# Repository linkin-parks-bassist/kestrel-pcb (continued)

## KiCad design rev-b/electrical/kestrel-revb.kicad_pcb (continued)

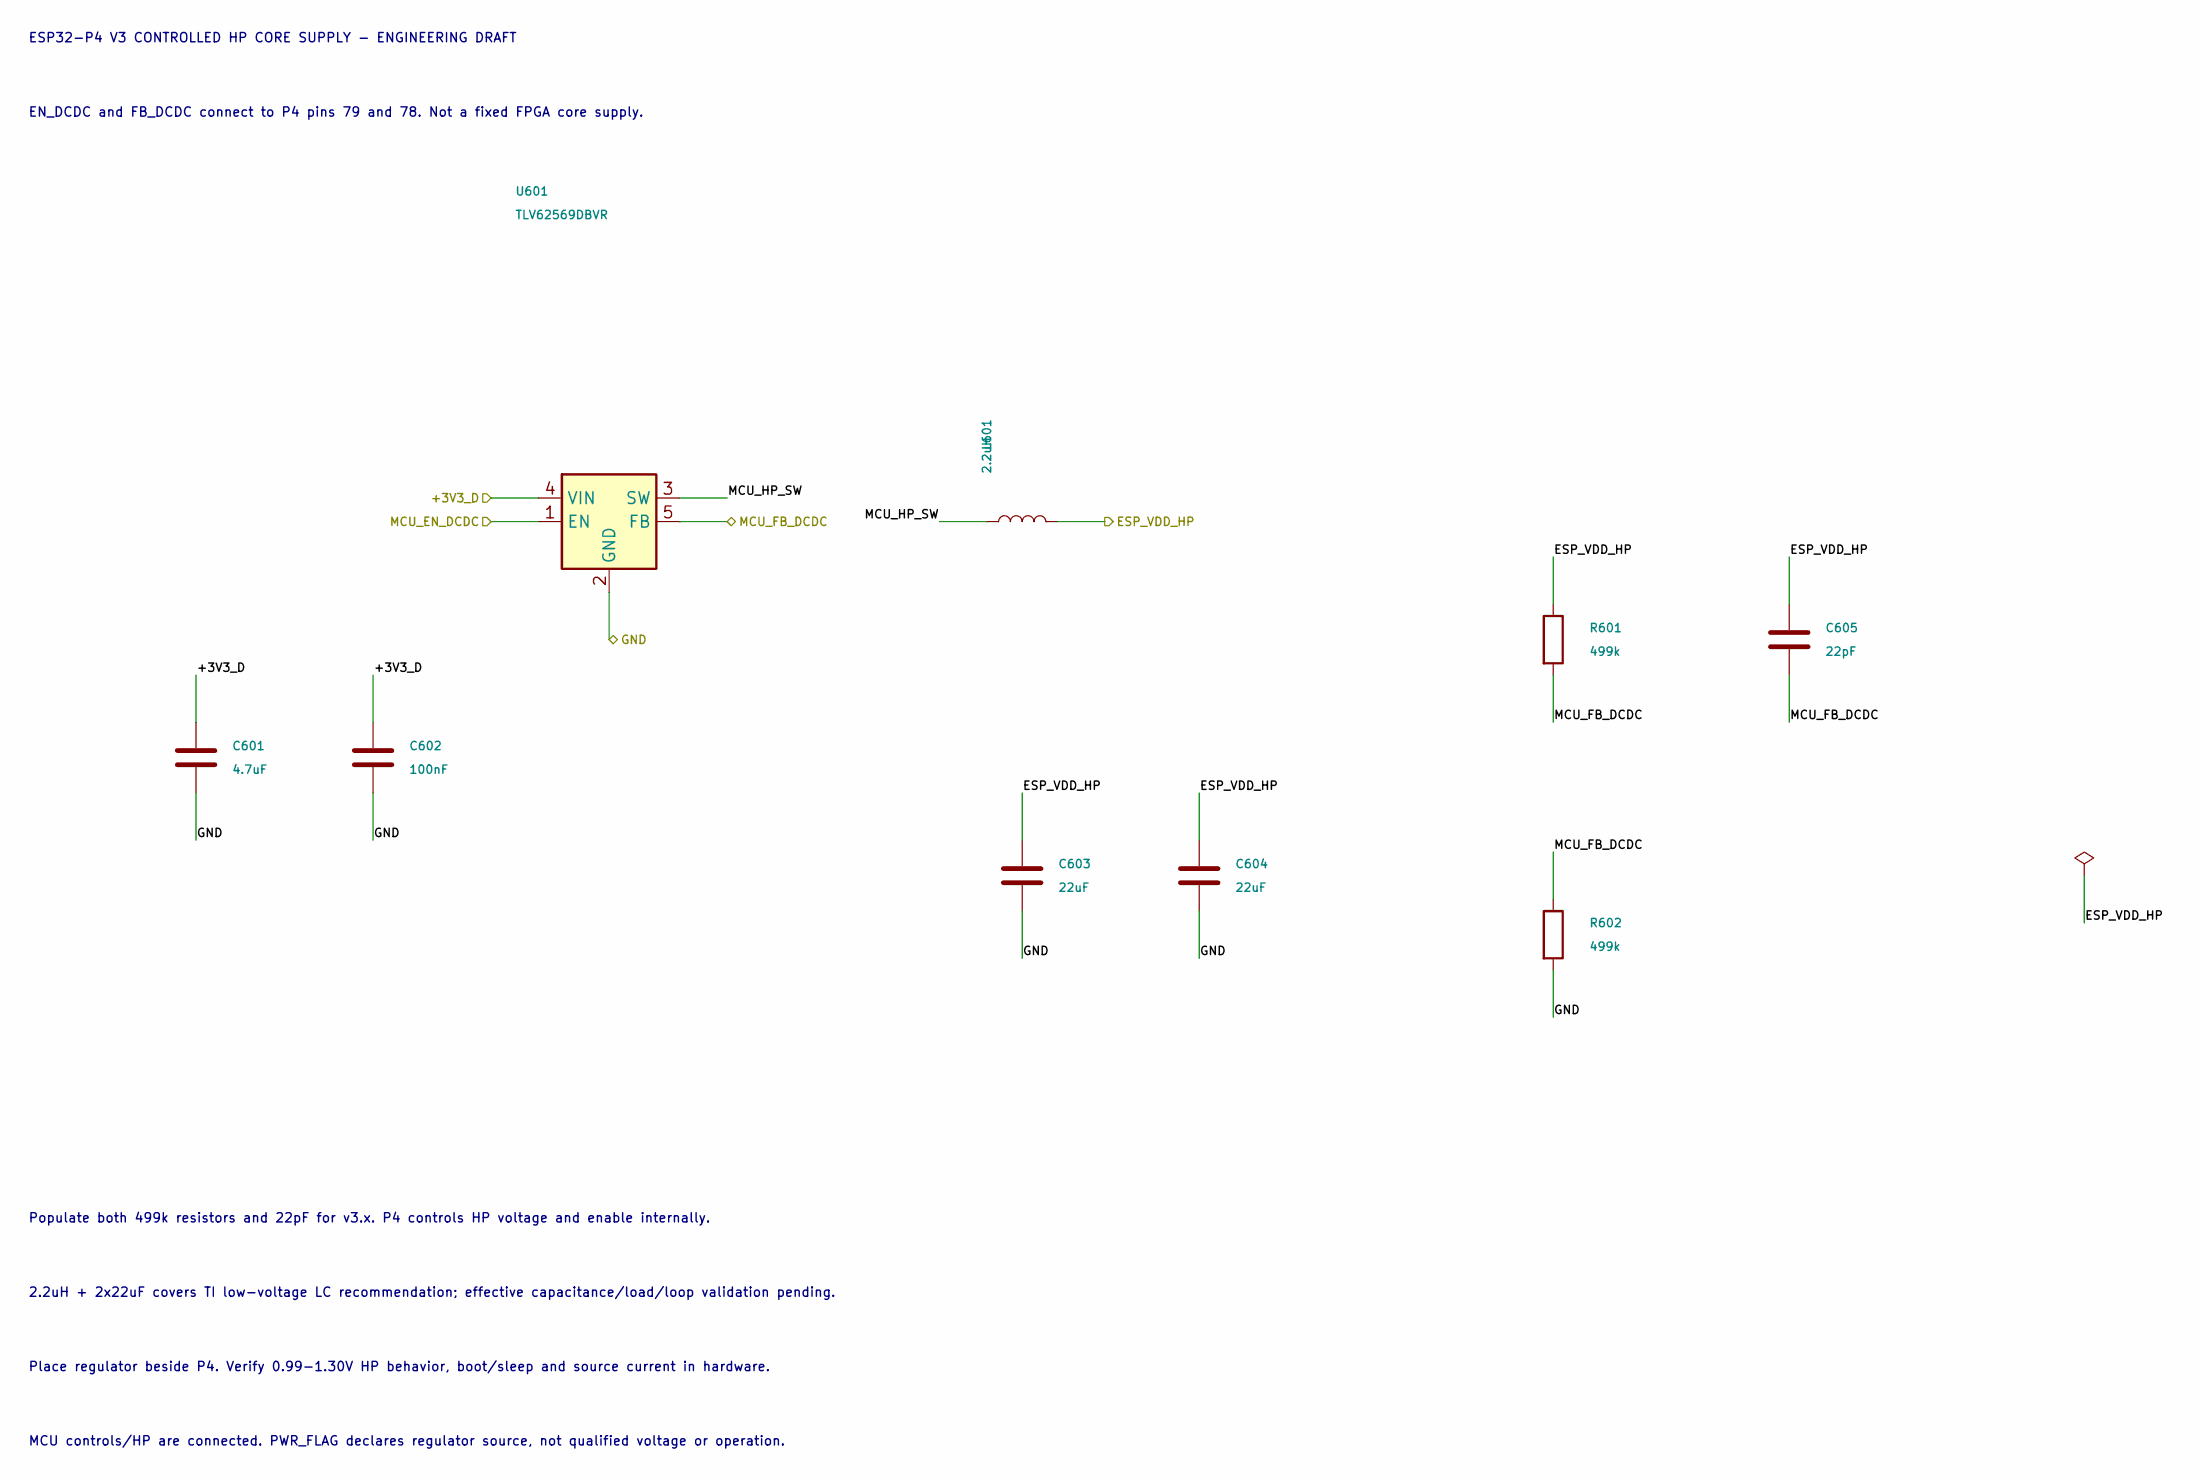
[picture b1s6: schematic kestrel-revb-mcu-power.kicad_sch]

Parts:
C601: 4.7uF; C_1210_3225Metric; Rating 4.7uF / 16V X7R
C602: 100nF; C_0603_1608Metric; Rating 100nF / 16V X7R
C603, C604: 22uF; C_1210_3225Metric; Rating 22uF / 16V X7R
C605: 22pF; C_0603_1608Metric; Rating 22pF / 25V C0G
L601: 2.2uH; L_Sunlord_MWSA0402S; Rating 2.2uH / shielded / Isat >=3.5A; MPN MWSA0402S-2R2MT; LCSC C408335
R601, R602: 499k; R_0603_1608Metric; Rating 499k / 1%
U601: TLV62569DBVR; SOT-23-5

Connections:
/+3V3_D: C601.1, C602.1, U601.4 (VIN); also elsewhere on the board
/ESP_VDD_HP: C603.1, C604.1, C605.1, L601.2, R601.1; also elsewhere on the board
/GND: C601.2, C602.2, C603.2, C604.2, R602.2, U601.2 (GND); also elsewhere on the board
/MCU_EN_DCDC: U601.1 (EN); also elsewhere on the board
/MCU_FB_DCDC: C605.2, R601.2, R602.1, U601.5 (FB); also elsewhere on the board
/P4 controlled HP regulator/MCU_HP_SW: L601.1, U601.3 (SW)

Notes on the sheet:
ESP32-P4 V3 CONTROLLED HP CORE SUPPLY - ENGINEERING DRAFT
EN_DCDC and FB_DCDC connect to P4 pins 79 and 78. Not a fixed FPGA core supply.
Populate both 499k resistors and 22pF for v3.x. P4 controls HP voltage and enable internally.
2.2uH + 2x22uF covers TI low-voltage LC recommendation; effective capacitance/load/loop validation pending.
Place regulator beside P4. Verify 0.99-1.30V HP behavior, boot/sleep and source current in hardware.
MCU controls/HP are connected. PWR_FLAG declares regulator source, not qualified voltage or operation.
